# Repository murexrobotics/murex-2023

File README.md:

# MUREX ROV 2022-2023

Codebase for the MUREX 2023 ROV for the MATE Underwater Robotics Competition.

## Table of Contents
- [Setup](Setup)
- [Usage](Usage)
- [Design](Design)
- [License](License)

## Setup
To use properly use the Murex codebase the user must have some software installed in addition to the MUREX codebase.

### Dev Dependencies
- [Python](https://www.python.org/downloads/) v3.9 (Or Newer)
- [NodeJS](https://nodejs.org/en/download) v18.6.1 (Or Newer)
- [FFmpeg](https://ffmpeg.org/download.html) v5.1.2 (Or Newer)

### Installation
```Bash
git clone https://github.com/murexrobotics/murex-2023.git
cd murex-2023
python3 -m pip install -r requirements.txt
cd web-interface
npm i
cd ../
```

## Usage

For optimal usage, start topside, then aquatic then web-interface.

### Topside
```Python
python3 topside
```

### Aquatic
```Bash
python3 aquatic
```

### Web Interface
```Bash
cd web-interface
npm run dev
```

## Design
This is a brief overview of how the ROV was designed.

### Mechanical
[ROV CAD](https://cad.onshape.com/documents/f2c5e508349c88b025f713bf/w/5608aa019685f90fd8c58b6c/e/0061e131f16a5293ec96639c)
### Programming
| Codebase | Role |
|----------|------|
| [Aquatic](https://github.com/murexrobotics/murex-2023/tree/main/aquatic) | Handles interfacing with sensors and thrusters. Control of ROV. |
| [Topside](https://github.com/murexrobotics/murex-2023/tree/main/topside) | Decodes control input and overall ROV control signals. |
| [Web Interface](https://github.com/murexrobotics/murex-2023/tree/main/web-interface) | Displays telemetry data from ROV for realtime monitoring and emergency control. |
### Electrical

| PCB | Role |
|-----|------|
| Integration PCB | Supply power to all components, sensors and PWM signal generator. |
| ESC Integration PCB | Connects directly to ESC's and Integration PCB to make connecting ESC's easier. **Was not used in final revision** |

## License

Licensed under the [MIT](LICENSE) License

Copyright (c) 2023 MUREX Robotics

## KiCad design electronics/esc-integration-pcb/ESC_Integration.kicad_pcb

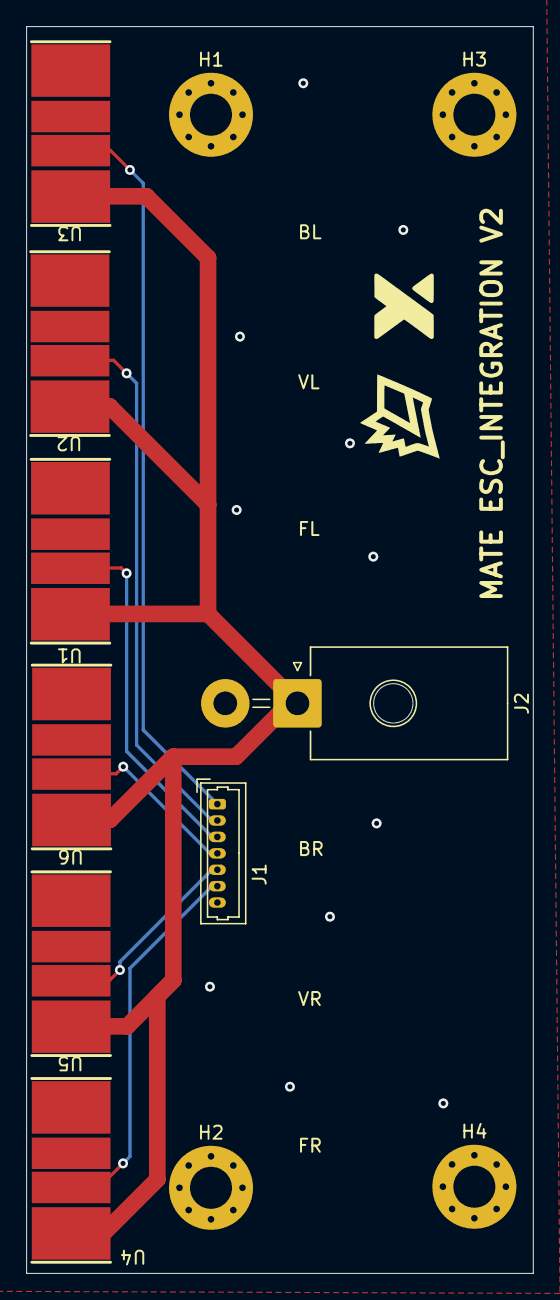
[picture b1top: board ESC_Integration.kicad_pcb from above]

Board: 2 copper layers, 38.6 x 95.0 mm, 12 parts (0 on the bottom side), 8 nets.

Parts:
H1, H2, H3, H4: MountingHole; MountingHole_3.2mm_M3_Pad_Via
J1: Conn_01x07; Molex_PicoBlade_53047-0710_1x07_P1.25mm_Vertical
J2: Conn_01x02; Molex_Mega-Fit_76825-0002_2x01_P5.70mm_Horizontal
U1, U2, U3, U4, U5, U6: ESC

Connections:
GND: J1.7, J2.2, U1.6 (VIN), U2.6 (VIN), U3.6 (VIN), U4.6 (VIN), U5.6 (VIN), U6.6 (VIN)
PWM_BL: J1.1, U3.5 (PWM)
PWM_BR: J1.4, U6.5 (PWM)
PWM_FL: J1.3, U1.5 (PWM)
PWM_FR: J1.6, U4.5 (PWM)
PWM_VL: J1.2, U2.5 (PWM)
PWM_VR: J1.5, U5.5 (PWM)
VIN: J2.1, U1.4 (GND), U2.4 (GND), U3.4 (GND), U4.4 (GND), U5.4 (GND), U6.4 (GND)

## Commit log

2023-03-06 <MIGRATE>(ALL): migrating code to organization
2023-03-06 <MIGRATE>(ALL): migrating codebase to organization
2023-03-06 Split ffmpeg files into rpi and topside computer
2023-03-06 <REFACTOR>(INTEGRATION): moved integration to corresponding folders, initialized web interface
2023-03-06 <FEAT>(web interface): web interface working, features not implemented
2023-03-07 Specified project dependencies
2023-03-07 Changed order of some stuff so I could think better
2023-03-07 Abstracted BME680 functionality
2023-03-07 Abstracted Camera movement functionality
2023-03-07 Abstracted Gamepad functionality (no pygame yet)
2023-03-07 Abstracted thruster functionality
2023-03-07 Moved pixel stuff
2023-03-07 Turned folder into python module
2023-03-07 moved i2c init to main + fixed camera and thruster init
2023-03-08 removed whitespace
2023-03-08 Added telemetry output
2023-03-08 WIP sending telemetry data
2023-03-10 Some changes to motor.py
2023-03-14 abstract i2c initialization into own module
2023-03-14 Abstract initialization and deinitialization of PCA9685
2023-03-14 Refactored, no longer class based
2023-03-14 Refactor to remove class + Docs
2023-03-14 Typo in docs
2023-03-14 Update usages with new interfaces
2023-03-16 FEAT(TOPSIDE): added realtime charts (doesn't work yet)
2023-03-16 FIX(INTERFACE): fixed live-update charts
    formatted code
2023-03-17 FIX(TOPSIDE): made code more concise
2023-03-17 FIX(CAMERA): improved latency and video quality; optimized ffplay
2023-03-17 Fix(Docs): Fixed legacy function name in thruster docs
2023-03-17 Update: Changed color api to enforce use of ky word args (kwargs)
2023-03-20 Update: Added testing code
2023-03-25 Thrusters(Rewrite): Access duty cycle directly, not through Servo
2023-03-25 Docs(Update): More consts + Fixed outdated usage
2023-03-26 Update(Thrusters): Removed references to adafruit servo api
2023-03-26 New(Telemetry): UNTESTED - Aggregates data from components, sends over WS
2023-04-08 Refactor(Testing): Better logging + testing moved function
2023-04-08 New(Telemetry): Stream + Docs
2023-04-08 Fix(Formatting): Removed empty lines
2023-04-09 FIX(ESP32): fixed web interface displaying real time
2023-04-09 FIX(INTERFACE): prototype dashboard
2023-04-10 New(Thruster): Interpolation function for smooth speed change
2023-04-10 Test(Telemtry): For testing telemtry, to be deleted
2023-04-11 Update(Log): Subbed for colored logging output
2023-04-13 Feat: Implement integrated event loop
2023-04-13 Fix: Thruster channels
2023-04-13 Fix: Removed node modules from repo
2023-04-13 Fix: Remove node modules
2023-04-13 Fix(Port): Changed address form localhost to IP
2023-04-13 Fix: Event loop
2023-04-14 FEAT(TOPSIDE): Status Report (unstyled) and Restart Pi
2023-04-14 FIX(TOPSIDE) Status Report style
2023-04-14 Fix(Telemetry): Fix names
2023-04-15 Restructure(Core): Removed old code, moved old code up
2023-04-15 Restructure: Prune old code
2023-04-16 Feat(Topside): Update & Restart thru interface
2023-04-16 FIX(Aquatic): Camera combined code updated
2023-04-16 Fix(Topside): Backup Signals sent through CGI script
2023-04-16 Feat(Core): Basic controller decoding relay and execution
2023-04-16 Fix: Reorder thruster channels to align with code
2023-04-17 Update: Docs + gracefull exit handling
2023-04-17 Refactor: Comments + moving around code
2023-04-17 Update: Thruster update loop
2023-04-17 Refactor: Aquatic Event loop
2023-04-17 feat: Copy logging code from aquatic
2023-04-18 Fix(Interface): Backup Signal Constants Corrected
2023-04-18 Fix(Interface): New Constants to update
2023-04-19 Fix(Interface): Backup signal telemetry updated
2023-04-19 Feat: Integrate Video streaming into topside
2023-04-20 Fix(Interface): Backup Signals no longer dependent on CGI
2023-04-21 Feat: Controller Decoding + Thrust Interpolation
2023-04-22 feat(arm): Implement arm control mechanics
2023-04-22 Fix(Log): Debug log messages
2023-04-22 Refactor: Added features for clarity
2023-05-01 Fix: Arm + Thruster Callibration
2023-05-01 Refactor: Removed dead/ old code
2023-05-01 Refactor: Move sub-modules to root + rename
2023-05-01 Docs: Update docs
2023-05-01 Refactor: Moved/ deleted code to improve structure
2023-05-01 Docs: Fixed description
2023-05-01 Feat: Added License
2023-05-01 Docs: Readme
2023-05-01 Docs: Update Readme
2023-05-01 Docs: Updated Readme
2023-05-02 Fix(Docs): Typo in Readme
2023-05-02 Fix(Docs): Update MUREX logo path
2023-05-02 Feat(Docs): Add rough structure of electrical, mech and programming
2023-05-02 Feat: Added schematics to repo
